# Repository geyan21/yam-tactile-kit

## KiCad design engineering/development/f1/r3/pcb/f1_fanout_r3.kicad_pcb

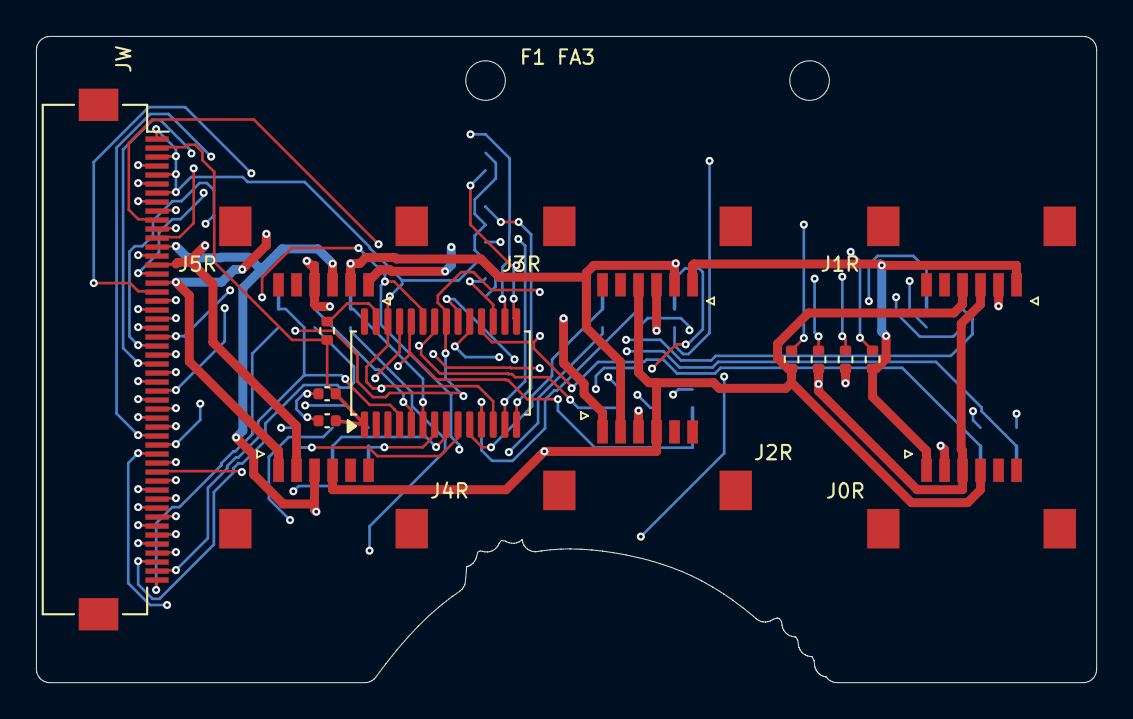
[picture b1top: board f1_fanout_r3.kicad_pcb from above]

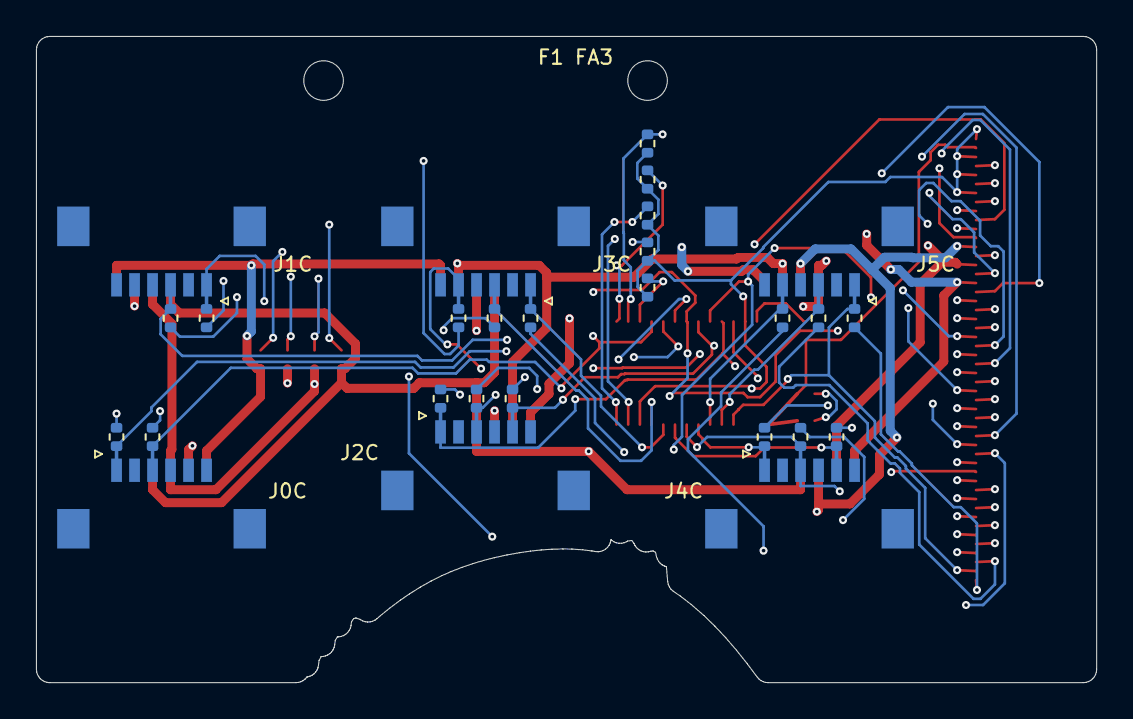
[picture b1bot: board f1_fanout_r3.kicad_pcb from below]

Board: 4 copper layers, 58.9 x 35.9 mm, 44 parts (27 on the bottom side), 48 nets.

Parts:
CT1: 100 nF X7R 10 V; CT1
CT2: 1 uF X7R 10 V; CT2
H1, H2: M2 clearance; MOUNT_M2
J0C: FH12-6S-1SH(1)(98); J0C
J0R: FH12-6S-1SH(1)(98); J0R
J1C: FH12-6S-1SH(1)(98); J1C
J1R: FH12-6S-1SH(1)(98); J1R
J2C: FH12-6S-1SH(1)(98); J2C
J2R: FH12-6S-1SH(1)(98); J2R
J3C: FH12-6S-1SH(1)(98); J3C
J3R: FH12-6S-1SH(1)(98); J3R
J4C: FH12-6S-1SH(1)(98); J4C
J4R: FH12-6S-1SH(1)(98); J4R
J5C: FH12-6S-1SH(1)(98); J5C
J5R: FH12-6S-1SH(1)(98); J5R
JW: FH12-50S-0.5SH(55); JW
RKC0: 0 ohm sense pickoff; RKC0
RKC1: 0 ohm sense pickoff; RKC1
RKC2: 0 ohm sense pickoff; RKC2
RKC3: 0 ohm sense pickoff; RKC3
RKC4: 0 ohm sense pickoff; RKC4
RKC5: 0 ohm sense pickoff; RKC5
RKC6: 0 ohm sense pickoff; RKC6
RKC7: 0 ohm sense pickoff; RKC7
RKC8: 0 ohm sense pickoff; RKC8
RKC9: 0 ohm sense pickoff; RKC9
RKC10: 0 ohm sense pickoff; RKC10
RKC11: 0 ohm sense pickoff; RKC11
RKC12: 0 ohm sense pickoff; RKC12
RKC13: 0 ohm sense pickoff; RKC13
RKC14: 0 ohm sense pickoff; RKC14
RKC15: 0 ohm sense pickoff; RKC15
RKR0: 0 ohm sense pickoff; RKR0
RKR1: 0 ohm sense pickoff; RKR1
RKR2: 0 ohm sense pickoff; RKR2
RKR3: 0 ohm sense pickoff; RKR3
RP0: 100k; RP0
RP1: 100k; RP1
RP2: 100k; RP2
RP3: 100k; RP3
RP4: 100k; RP4
RT: 10.0k 0.1% 25ppm/K; RT
UT: ADG706BRUZ; UT

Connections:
+3V3: CT1.1, CT2.1, JW.2, RT.1, UT.1
A0: JW.4, RP0.1, UT.16
A1: JW.6, RP1.1, UT.15
A2: JW.8, RP2.1, UT.14
A3: JW.9, RP3.1, UT.13
C0_I: J0C.3, JW.19, RKC0.1, UT.18
C0_S: JW.20, RKC0.2
C1_I: J0C.1, JW.21, RKC1.1, UT.19
C1_S: JW.22, RKC1.2
C2_I: J1C.3, JW.23, RKC2.1, UT.20
C2_S: JW.24, RKC2.2
C3_I: J1C.1, JW.25, RKC3.1, UT.21
C3_S: JW.26, RKC3.2
C4_I: J2C.5, JW.27, RKC4.1, UT.22
C4_S: JW.28, RKC4.2
C5_I: J2C.3, JW.29, RKC5.1, UT.23
C5_S: JW.30, RKC5.2
C6_I: J2C.1, JW.31, RKC6.1, UT.24
C6_S: JW.32, RKC6.2
C7_I: J3C.5, JW.33, RKC7.1, UT.25
C7_S: JW.34, RKC7.2
C8_I: J3C.3, JW.35, RKC8.1, UT.11
C8_S: JW.36, RKC8.2
C9_I: J3C.1, JW.37, RKC9.1, UT.10
C9_S: JW.38, RKC9.2
C10_I: J4C.5, JW.39, RKC10.1, UT.9
C10_S: JW.40, RKC10.2
C11_I: J4C.3, JW.41, RKC11.1, UT.8
C11_S: JW.42, RKC11.2
C12_I: J4C.1, JW.43, RKC12.1, UT.7
C12_S: JW.44, RKC12.2
C13_I: J5C.5, JW.45, RKC13.1, UT.6
C13_S: JW.46, RKC13.2
C14_I: J5C.3, JW.47, RKC14.1, UT.5
C14_S: JW.48, RKC14.2
C15_I: J5C.1, JW.49, RKC15.1, UT.4
C15_S: JW.50, RKC15.2
GND: CT1.2, CT2.2, JW.1, JW.3, JW.5, JW.7, RP0.2, RP1.2, RP2.2, RP3.2, RP4.2, UT.12, UT.26
R0_I: J0R.4, J1R.4, J2R.4, J3R.4, J4R.4, J5R.4, JW.11, RKR0.1
R0_S: JW.12, RKR0.2
R1_I: J0R.3, J1R.3, J2R.3, J3R.3, J4R.3, J5R.3, JW.13, RKR1.1
R1_S: JW.14, RKR1.2
R2_I: J0R.2, J1R.2, J2R.2, J3R.2, J4R.2, J5R.2, JW.15, RKR2.1
R2_S: JW.16, RKR2.2
R3_I: J0R.1, J1R.1, J2R.1, J3R.1, J4R.1, J5R.1, JW.17, RKR3.1
R3_S: JW.18, RKR3.2
TEST_D: RT.2, UT.27
TEST_EN: JW.10, RP4.1, UT.17

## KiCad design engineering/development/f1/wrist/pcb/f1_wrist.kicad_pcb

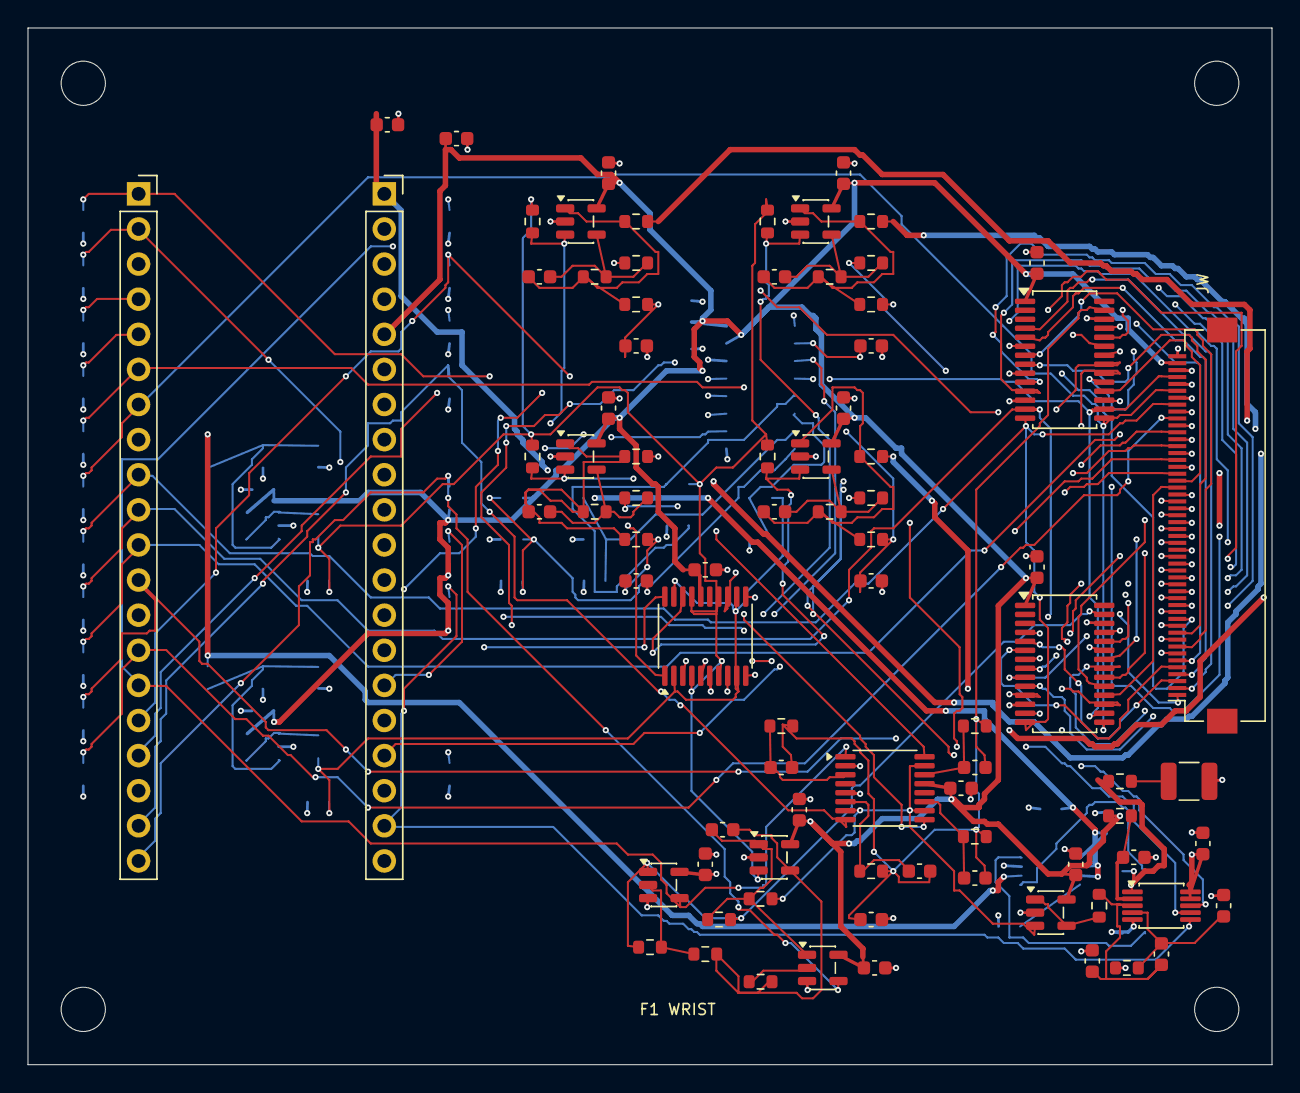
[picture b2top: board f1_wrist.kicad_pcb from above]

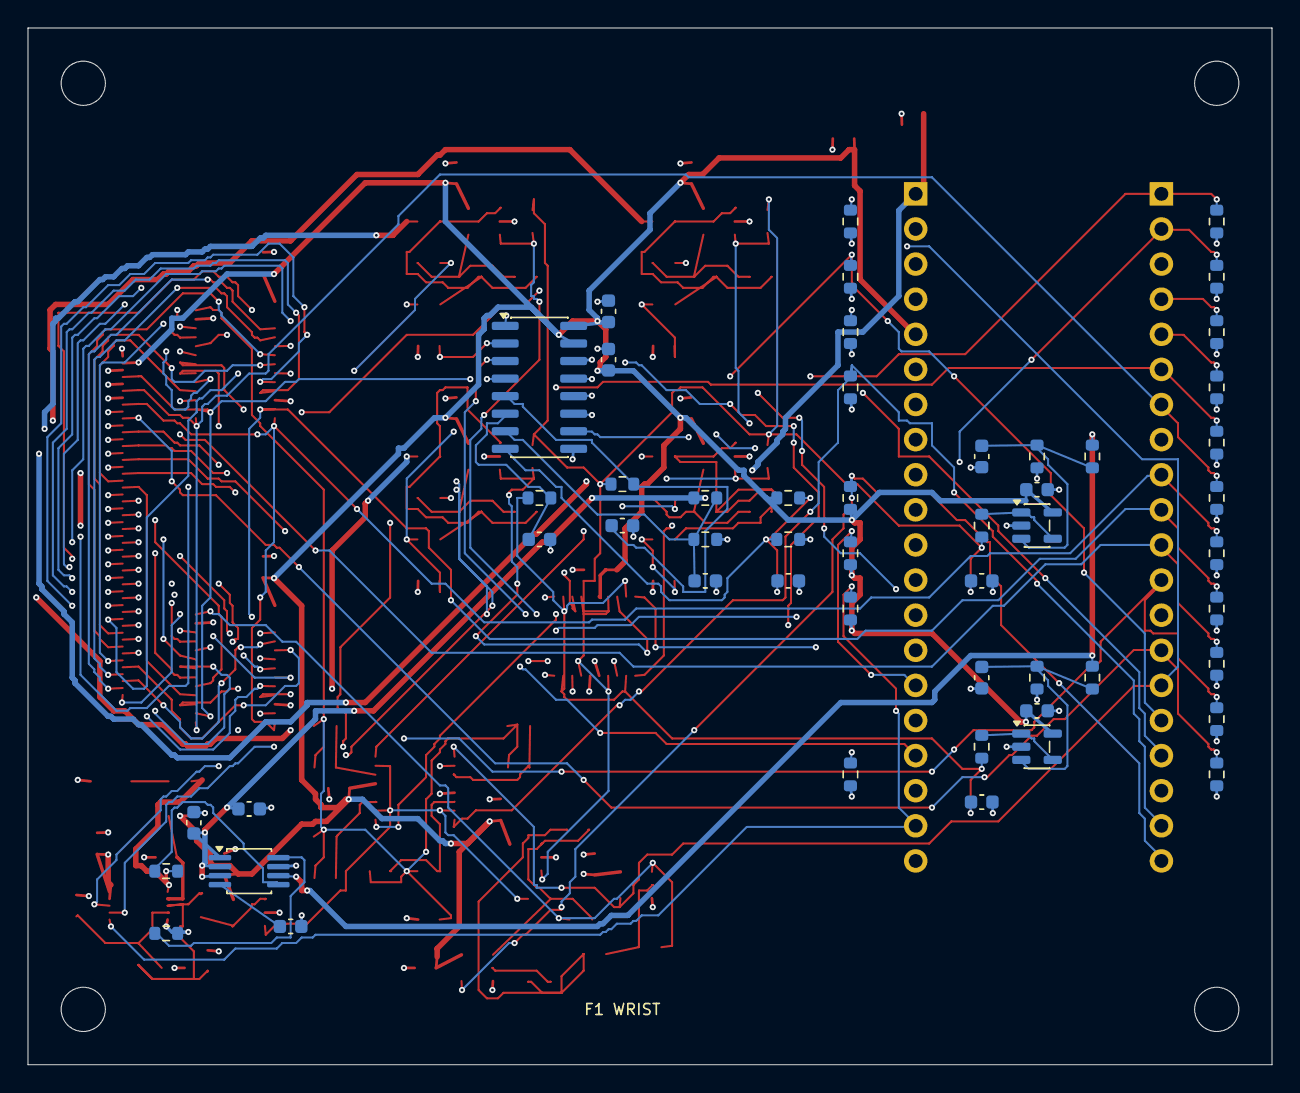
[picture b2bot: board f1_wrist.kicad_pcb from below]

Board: 4 copper layers, 90.0 x 75.0 mm, 139 parts (52 on the bottom side), 110 nets.

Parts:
CADCD: 2.2n C0G; CADCD
CADCN: 2.2n C0G; CADCN
CADCP: 2.2n C0G; CADCP
CAVDD: 1u X7R 10V; CAVDD
CBIASIN: 100n X7R 10V; CBIASIN
CBIASOUT: 100n X7R 10V; CBIASOUT
CBMON: 1u X7R 10V; CBMON
CBULK3: 10u X7R 10V; CBULK3
CBULK5: 4.7u X7R 10V; CBULK5
CCURRENT: 3.3n C0G; CCURRENT
CDAB: 100n X7R 10V; CDAB
CDBIAS: 100n X7R 10V; CDBIAS
CDBYP: 100n X7R 10V; CDBYP
CDEXC: 100n X7R 10V; CDEXC
CDGAIN: 100n X7R 10V; CDGAIN
CDMON: 100n X7R 10V; CDMON
CDPARK: 100n X7R 10V; CDPARK
CDR0: 100n X7R 10V; CDR0
CDR1: 100n X7R 10V; CDR1
CDR2: 100n X7R 10V; CDR2
CDR3: 100n X7R 10V; CDR3
CDTIA: 100n X7R 10V; CDTIA
CDVDD: 1u X7R 10V; CDVDD
CEXCIN: 100n X7R 10V; CEXCIN
CEXCOUT: 100n X7R 10V; CEXCOUT
CFB0: 100p C0G; CFB0
CFB1: 100p C0G; CFB1
CFB2: 100p C0G; CFB2
CFB3: 100p C0G; CFB3
CFILT: 2.2u X7R 10V; effective >=1u; CFILT
CLOCAL: 15p C0G; CLOCAL
CMB: 10n X7R 10V; CMB
CME: 10n X7R 10V; CME
CMON0: 10n X7R 10V; CMON0
CMON1: 10n X7R 10V; CMON1
CMON2: 10n X7R 10V; CMON2
CMON3: 10n X7R 10V; CMON3
CREF: 22u X7R 25V; effective 10-47u verified; CREF
CREFIN1: 100n X7R 10V; CREFIN1
CREFIN2: 1u X7R 10V; CREFIN2
CRSEL: 100n X7R 10V; CRSEL
CTIA0: 470p C0G; CTIA0
CTIA1: 150p C0G; CTIA1
CTIA2: 68p C0G; CTIA2
CTIA3: 56p C0G; CTIA3
CUCI: 100n X7R 10V; CUCI
CUCS: 100n X7R 10V; CUCS
CV3: 10n X7R 10V; CV3
CV5: 10n X7R 10V; CV5
H1, H2, H3, H4: (no value)
JP1: 1x20 female socket 2.54 mm; Pico header; JP1
JP2: 1x20 female socket 2.54 mm; Pico header; JP2
JW: FH12-50S-0.5SH(55); JW
PD_A0: 100k; PD_A0
PD_A1: 100k; PD_A1
PD_A2: 100k; PD_A2
PD_A3: 100k; PD_A3
PD_CUR_EN: 100k; PD_CUR_EN
PD_GAIN0: 100k; PD_GAIN0
PD_GAIN1: 100k; PD_GAIN1
PD_GAIN2: 100k; PD_GAIN2
PD_GAIN3: 100k; PD_GAIN3
PD_MISO: 100k; PD_MISO
PD_ROW0: 100k; PD_ROW0
PD_ROW1: 100k; PD_ROW1
PD_ROW2: 100k; PD_ROW2
PD_ROW3: 100k; PD_ROW3
PD_SNS_EN: 100k; PD_SNS_EN
PD_TEST_EN: 100k; PD_TEST_EN
PU_ADC_CONV: 100k; PU_ADC_CONV
PU_MON_CS: 100k; PU_MON_CS
PU_PARK: 100k; PU_PARK
RACTIVEPARK: 1k; RACTIVEPARK
RADCN: 22 0.1%; RADCN
RADCP: 22 0.1%; RADCP
RAVDD: 2.2; RAVDD
RBIAS0: 1M; RBIAS0
RBIAS1: 1M; RBIAS1
RBIAS2: 1M; RBIAS2
RBIAS3: 1M; RBIAS3
RBIASB: 10000 0.01% 10ppm/K; RBIASB
RBIASOUT: 47; RBIASOUT
RBIAST: 10000 0.01% 10ppm/K; RBIAST
RBOOST: 680; RBOOST
REXCB: 17000 0.01% 10ppm/K; REXCB
REXCOUT: 47; REXCOUT
REXCT: 16000 0.01% 10ppm/K; REXCT
RFB0: 100M; RFB0
RFB1: 100M; RFB1
RFB2: 100M; RFB2
RFB3: 100M; RFB3
RGNDS: 0 sense pickup; RGNDS
RINPUT: 300; RINPUT
RISO0: 47; RISO0
RISO1: 47; RISO1
RISO2: 47; RISO2
RISO3: 47; RISO3
RMB: 4.7k; RMB
RME: 4.7k; RME
RMON0: 4.7k; RMON0
RMON1: 4.7k; RMON1
RMON2: 4.7k; RMON2
RMON3: 4.7k; RMON3
ROUT: 0.1; ROUT
RPARK: 100M; RPARK
RREFESR: 0.047 1%; RREFESR
RREFS: 0 sense pickup; RREFS
RSNS0: 4700; RSNS0
RSNS1: 4700; RSNS1
RSNS2: 4700; RSNS2
RSNS3: 4700; RSNS3
RTIA0: 499 0.1%; RTIA0
RTIA1: 4990 0.1%; RTIA1
RTIA2: 24900 0.1%; RTIA2
RTIA3: 39200 0.1%; RTIA3
RV3B: 10k 0.1%; RV3B
RV3T: 10k 0.1%; RV3T
RV5B: 10k 0.1%; RV5B
RV5T: 10k 0.1%; RV5T
UAB: OPA320AQDBVRQ1; UAB
UADC: ADS8866IDGSR; UADC
UBIAS: OPA392DBVR; UBIAS
UBYP: TMUX1102DBVR; UBYP
UCI: ADG706BRUZ; UCI
UCS: ADG706BRUZ; UCS
UEXC: OPA392DBVR; UEXC
UGAIN: TMUX1112PWR; UGAIN
UMON: MCP3208-B/SL; UMON
UPARK: TMUX1101DBVR; UPARK
UR0: OPA392DBVR; UR0
UR1: OPA392DBVR; UR1
UR2: OPA392DBVR; UR2
UR3: OPA392DBVR; UR3
UREF: REF6033IDGKR; UREF
URSEL: TMUX1134PWR; URSEL
UTIA: OPA392DBVR; UTIA

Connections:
+3V3: CBMON.1, CBULK3.1, CDAB.1, CDBIAS.1, CDBYP.1, CDEXC.1, CDGAIN.1, CDMON.1, CDPARK.1, CDR0.1, CDR1.1, CDR2.1, CDR3.1, CDTIA.1, CDVDD.1, CRSEL.1, CUCI.1, CUCS.1, JP2.5, JW.49, PU_ADC_CONV.2, PU_MON_CS.2, PU_PARK.2, RAVDD.1, RV3T.1, UAB.5, UADC.9, UADC.10, UBIAS.5, UBYP.5, UCI.1, UCS.1, UEXC.5, UGAIN.13, UMON.15, UMON.16, UPARK.5, UR0.5, UR1.5, UR2.5, UR3.5, URSEL.16, UTIA.5
+3V3_DIV2: CV3.1, RV3B.1, RV3T.2, UMON.8
+5V: CBULK5.1, CREFIN1.1, CREFIN2.1, JP2.1, RV5T.1, UREF.1, UREF.2, UREF.3
+5V_DIV2: CV5.1, RV5B.1, RV5T.2, UMON.7
A0: JP1.6, JW.47, PD_A0.1, UCI.16, UCS.16
A1: JP1.7, JW.45, PD_A1.1, UCI.15, UCS.15
A2: JP1.9, JW.43, PD_A2.1, UCI.14, UCS.14
A3: JP1.10, JW.42, PD_A3.1, UCI.13, UCS.13
ADC_AVDD: CAVDD.1, RAVDD.2, UADC.2
ADC_BUFFER: RADCP.1, UAB.1, UAB.4
ADC_CONV: JP2.19, PU_ADC_CONV.1, UADC.6
AINN: CADCD.2, CADCN.1, RADCN.2, UADC.4
AINP: CADCD.1, CADCP.1, RADCP.2, UADC.3
AMP_OUT: CLOCAL.1, ROUT.1, RPARK.1, UPARK.1, UTIA.1
BIAS_BUFFER: RBIASOUT.1, UBIAS.1, UBIAS.4
BIAS_DIV: CBIASIN.1, RBIASB.1, RBIAST.2, UBIAS.3
BIAS_MON: CMB.1, RMB.2, UMON.5
C0_I: JW.32, UCI.18
C0_S: JW.31, UCS.18
C1_I: JW.30, UCI.19
C1_S: JW.29, UCS.19
C2_I: JW.28, UCI.20
C2_S: JW.27, UCS.20
C3_I: JW.26, UCI.21
C3_S: JW.25, UCS.21
C4_I: JW.24, UCI.22
C4_S: JW.23, UCS.22
C5_I: JW.22, UCI.23
C5_S: JW.21, UCS.23
C6_I: JW.20, UCI.24
C6_S: JW.19, UCS.24
C7_I: JW.18, UCI.25
C7_S: JW.17, UCS.25
C8_I: JW.16, UCI.11
C8_S: JW.15, UCS.11
C9_I: JW.14, UCI.10
C9_S: JW.13, UCS.10
C10_I: JW.12, UCI.9
C10_S: JW.11, UCS.9
C11_I: JW.10, UCI.8
C11_S: JW.9, UCS.8
C12_I: JW.8, UCI.7
C12_S: JW.7, UCS.7
C13_I: JW.6, UCI.6
C13_S: JW.5, UCS.6
C14_I: JW.4, UCI.5
C14_S: JW.3, UCS.5
C15_I: JW.2, UCI.4
C15_S: JW.1, UCS.4
COMP_MID: RBOOST.2, RINPUT.1, UBYP.2
CURRENT_D: CCURRENT.1, CTIA0.2, CTIA1.2, CTIA2.2, CTIA3.2, RTIA0.2, RTIA1.2, RTIA2.2, RTIA3.2, UCI.27
CUR_EN: JP1.11, PD_CUR_EN.1, UCI.17
EXCITE_MON: CME.1, RME.2, UMON.6
EXC_BUFFER: REXCOUT.1, UEXC.1, UEXC.4
EXC_DIV: CEXCIN.1, REXCB.1, REXCT.2, UEXC.3
GAIN0: JP1.15, PD_GAIN0.1, UBYP.4, UGAIN.1
GAIN1: JP1.16, PD_GAIN1.1, UGAIN.16
GAIN2: JP1.17, PD_GAIN2.1, UGAIN.9
GAIN3: JP1.19, PD_GAIN3.1, UGAIN.8
GAIN_BRANCH0: CTIA0.1, RTIA0.1, UGAIN.3
GAIN_BRANCH1: CTIA1.1, RTIA1.1, UGAIN.14
GAIN_BRANCH2: CTIA2.1, RTIA2.1, UGAIN.11
GAIN_BRANCH3: CTIA3.1, RTIA3.1, UGAIN.6
GND: CADCN.2, CADCP.2, CAVDD.2, CBIASIN.2, CBIASOUT.2, CBMON.2, CBULK3.2, CBULK5.2, CCURRENT.2, CDAB.2, CDBIAS.2, CDBYP.2, CDEXC.2, CDGAIN.2, CDMON.2, CDPARK.2, CDR0.2, CDR1.2, CDR2.2, CDR3.2, CDTIA.2, CDVDD.2, CEXCIN.2, CEXCOUT.2, CFILT.2, CMB.2, CME.2, CMON0.2, CMON1.2, CMON2.2, CMON3.2, CREF.2, CREFIN1.2, CREFIN2.2, CRSEL.2, CUCI.2, CUCS.2, CV3.2, CV5.2, JP1.3, JP1.8, JP1.13, JP1.18, JP2.3, JP2.8, JP2.13, JP2.18, JW.44, JW.46, JW.48, JW.50, PD_A0.2, PD_A1.2, PD_A2.2, PD_A3.2, PD_CUR_EN.2, PD_GAIN0.2, PD_GAIN1.2, PD_GAIN2.2, PD_GAIN3.2, PD_MISO.2, PD_ROW0.2, PD_ROW1.2, PD_ROW2.2, PD_ROW3.2, PD_SNS_EN.2, PD_TEST_EN.2, RADCN.1, RBIASB.2, REXCB.2, RGNDS.2, RV3B.2, RV5B.2, UAB.2, UADC.5, UBIAS.2, UBYP.3, UCI.12, UCI.26, UCS.12, UCS.26, UEXC.2, UGAIN.5, UMON.9, UMON.14, UPARK.3, UR0.2, UR1.2, UR2.2, UR3.2, UREF.7, URSEL.5, URSEL.6, UTIA.2
MON_CS: JP2.15, PU_MON_CS.1, UMON.10
OUTPUT_BUS: ROUT.2, UAB.3, UGAIN.2, UGAIN.7, UGAIN.10, UGAIN.15
PARK: JP1.20, PU_PARK.1, UPARK.4
PARK_LINK: RACTIVEPARK.1, UPARK.2
R0_I: JW.40, RISO0.2
R0_S: JW.39, RSNS0.1
R1_I: JW.38, RISO1.2
R1_S: JW.37, RSNS1.1
R2_I: JW.36, RISO2.2
R2_S: JW.35, RSNS2.1
R3_I: JW.34, RISO3.2
R3_S: JW.33, RSNS3.1
REF_CAP: CREF.1, RREFESR.2
REF_FILT: CFILT.1, UREF.4
REF_GND_SENSE: RGNDS.1, UREF.8
ROW0: JP1.1, PD_ROW0.1, URSEL.1
ROW0_CMD: RBIAS0.1, UR0.3, URSEL.3
ROW0_FB: CFB0.2, RFB0.2, RSNS0.2, UR0.4
ROW0_MON: CMON0.1, RMON0.2, UMON.1
ROW0_OUT: CFB0.1, RFB0.1, RISO0.1, RMON0.1, UR0.1
ROW1: JP1.2, PD_ROW1.1, URSEL.10
ROW1_CMD: RBIAS1.1, UR1.3, URSEL.8
ROW1_FB: CFB1.2, RFB1.2, RSNS1.2, UR1.4
ROW1_MON: CMON1.1, RMON1.2, UMON.2
ROW1_OUT: CFB1.1, RFB1.1, RISO1.1, RMON1.1, UR1.1
ROW2: JP1.4, PD_ROW2.1, URSEL.11
ROW2_CMD: RBIAS2.1, UR2.3, URSEL.13
ROW2_FB: CFB2.2, RFB2.2, RSNS2.2, UR2.4
ROW2_MON: CMON2.1, RMON2.2, UMON.3
ROW2_OUT: CFB2.1, RFB2.1, RISO2.1, RMON2.1, UR2.1
ROW3: JP1.5, PD_ROW3.1, URSEL.20
ROW3_CMD: RBIAS3.1, UR3.3, URSEL.18
ROW3_FB: CFB3.2, RFB3.2, RSNS3.2, UR3.4
ROW3_MON: CMON3.1, RMON3.2, UMON.4
ROW3_OUT: CFB3.1, RFB3.1, RISO3.1, RMON3.1, UR3.1
SENSE_D: RBOOST.1, RPARK.2, UBYP.1, UCS.27
SNS_EN: JP1.12, PD_SNS_EN.1, UCS.17
SPI_MISO: JP2.20, PD_MISO.1, UADC.7, UMON.12
SPI_MOSI: JP2.16, UMON.11
SPI_SCK: JP2.17, UADC.8, UMON.13
TEST_EN: JP1.14, JW.41, PD_TEST_EN.1
TIA_FB: CLOCAL.2, RACTIVEPARK.2, RINPUT.2, UTIA.4
VBIAS: CBIASOUT.1, RBIAS0.2, RBIAS1.2, RBIAS2.2, RBIAS3.2, RBIASOUT.2, RMB.1, URSEL.4, URSEL.7, URSEL.14, URSEL.17, UTIA.3
VEXCITE: CEXCOUT.1, REXCOUT.2, RME.1, URSEL.2, URSEL.9, URSEL.12, URSEL.19
VREF33: RBIAST.1, REXCT.1, RREFESR.1, RREFS.2, UADC.1, UREF.6
VREF_SENSE: RREFS.1, UREF.5

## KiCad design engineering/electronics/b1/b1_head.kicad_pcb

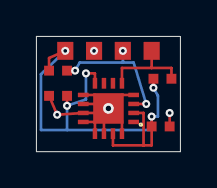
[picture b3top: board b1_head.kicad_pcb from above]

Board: 2 copper layers, 8.0 x 6.4 mm, 6 parts (0 on the bottom side), 4 nets.

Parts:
C1: 100nF 16V X7R 0402; C1
C2: 100nF 16V X7R 0402; C2
J1: Solder wires 3V3 GND SCL SDA; J1
R1: 10k 1% 0402; R1
R2: 10k 1% 0402; R2
U1: MLX90393SLW-ABA-011; U1

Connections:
3V3: C1.1, C2.2, J1.1, R1.1, R2.1, U1.2, U1.8, U1.15
GND: C1.2, C2.1, J1.2, U1.4, U1.9, U1.10, U1.11, U1.12, U1.13, U1.14, U1.16, U1.17
SCL: J1.3, R1.2, U1.3
SDA: J1.4, R2.2, U1.5

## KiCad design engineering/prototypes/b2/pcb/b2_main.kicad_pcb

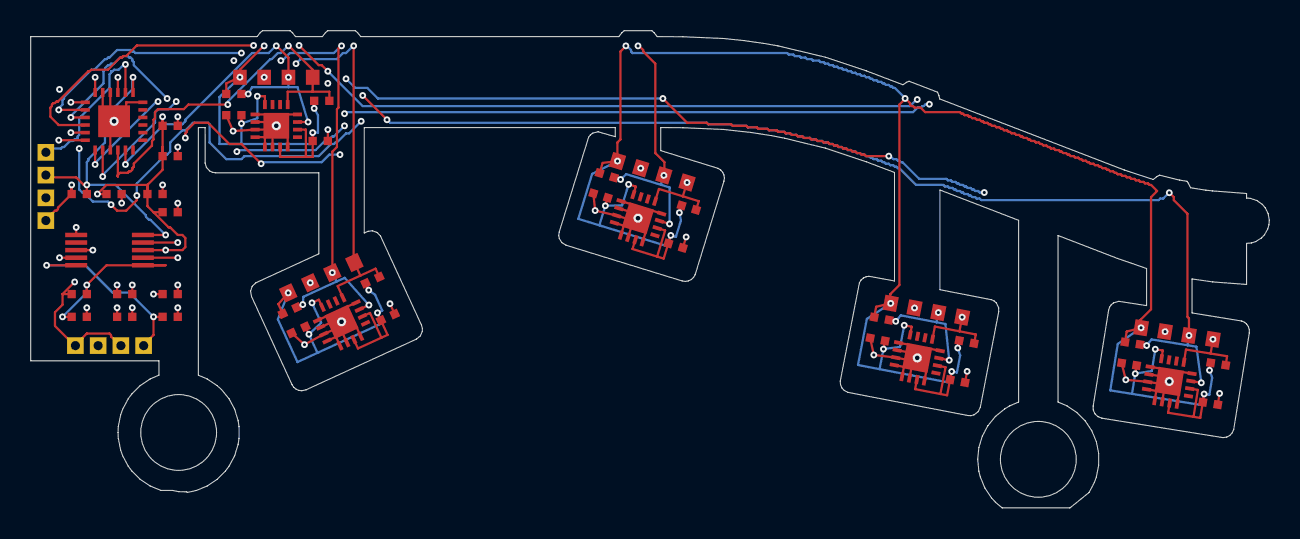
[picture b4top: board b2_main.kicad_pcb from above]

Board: 4 copper layers, 81.7 x 31.5 mm, 46 parts (0 on the bottom side), 19 nets.

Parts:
C11: 100nF 16V X7R 0402; C11
C12: 100nF 16V X7R 0402; C12
C21: 100nF 16V X7R 0402; C21
C22: 100nF 16V X7R 0402; C22
C31: 100nF 16V X7R 0402; C31
C32: 100nF 16V X7R 0402; C32
C41: 100nF 16V X7R 0402; C41
C42: 100nF 16V X7R 0402; C42
C51: 100nF 16V X7R 0402; C51
C52: 100nF 16V X7R 0402; C52
C100: 100nF 16V X7R 0402; C100
C101: 100nF 16V X7R 0402; C101
C102: 1uF 10V X7R 0402; C102
J1: Rear-exit solder wires; J1
J2: Rear-exit solder wires; J2
R11: 10k 1% 0402; R11
R12: 10k 1% 0402; R12
R21: 10k 1% 0402; R21
R22: 10k 1% 0402; R22
R31: 10k 1% 0402; R31
R32: 10k 1% 0402; R32
R41: 10k 1% 0402; R41
R42: 10k 1% 0402; R42
R51: 10k 1% 0402; R51
R52: 10k 1% 0402; R52
R100: 4.7k 1% 0402; R100
R101: 4.7k 1% 0402; R101
R102: 10k 1% 0402; R102
R103: 10k 1% 0402; R103
R104: 10k 1% 0402; R104
R105: 10k 1% 0402; R105
R106: 10k 1% 0402; R106
R107: 10k 1% 0402; R107
R108: 10k 1% 0402; R108
TP1: Solder wires 3V3 GND SCL SDA; TP1
TP2: Solder wires 3V3 GND SCL SDA; TP2
TP3: Solder wires 3V3 GND SCL SDA; TP3
TP4: Solder wires 3V3 GND SCL SDA; TP4
TP5: Solder wires 3V3 GND SCL SDA; TP5
U1: MLX90393SLW-ABA-011; U1
U2: MLX90393SLW-ABA-011; U2
U3: MLX90393SLW-ABA-011; U3
U4: MLX90393SLW-ABA-011; U4
U5: MLX90393SLW-ABA-011; U5
U10: TCA9548ARGER; U10
U11: ADS1115IDGSR; U11

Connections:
3V3: C11.1, C12.2, C21.1, C22.2, C31.1, C32.2, C41.1, C42.2, C51.1, C52.2, C100.1, C101.1, C102.1, J1.1, J2.1, J2.3, R11.1, R12.1, R21.1, R22.1, R31.1, R32.1, R41.1, R42.1, R51.1, R52.1, R100.1, R101.1, R102.1, R103.1, R105.1, TP1.1, TP2.1, TP3.1, TP4.1, TP5.1, U1.2, U1.8, U1.15, U2.2, U2.8, U2.15, U3.2, U3.8, U3.15, U4.2, U4.8, U4.15, U5.2, U5.8, U5.15, U10.21, U11.8
CHECK_HALF: R105.2, R106.1, U11.7
GND: C11.2, C12.1, C21.2, C22.1, C31.2, C32.1, C41.2, C42.1, C51.2, C52.1, C100.2, C101.2, C102.2, J1.2, R104.2, R106.2, R107.2, R108.2, TP1.2, TP2.2, TP3.2, TP4.2, TP5.2, U1.4, U1.9, U1.10, U1.11, U1.12, U1.13, U1.14, U1.16, U1.17, U2.4, U2.9, U2.10, U2.11, U2.12, U2.13, U2.14, U2.16, U2.17, U3.4, U3.9, U3.10, U3.11, U3.12, U3.13, U3.14, U3.16, U3.17, U4.4, U4.9, U4.10, U4.11, U4.12, U4.13, U4.14, U4.16, U4.17, U5.4, U5.9, U5.10, U5.11, U5.12, U5.13, U5.14, U5.16, U5.17, U10.9, U10.18, U10.22, U10.23, U10.25, U11.1, U11.3
RESET: R102.2, U10.24
SCL: J1.3, R100.2, U10.19, U11.10
SCL0: R11.2, TP1.3, U1.3, U10.2
SCL1: R21.2, TP2.3, U2.3, U10.4
SCL2: R31.2, TP3.3, U3.3, U10.6
SCL3: R41.2, TP4.3, U4.3, U10.8
SCL4: R51.2, TP5.3, U5.3, U10.11
SDA: J1.4, R101.2, U10.20, U11.9
SDA0: R12.2, TP1.4, U1.5, U10.1
SDA1: R22.2, TP2.4, U2.5, U10.3
SDA2: R32.2, TP3.4, U3.5, U10.5
SDA3: R42.2, TP4.4, U4.5, U10.7
SDA4: R52.2, TP5.4, U5.5, U10.10
T0: J2.2, R107.1, U11.4
T1: J2.4, R108.1, U11.5
VDD_HALF: R103.2, R104.1, U11.6

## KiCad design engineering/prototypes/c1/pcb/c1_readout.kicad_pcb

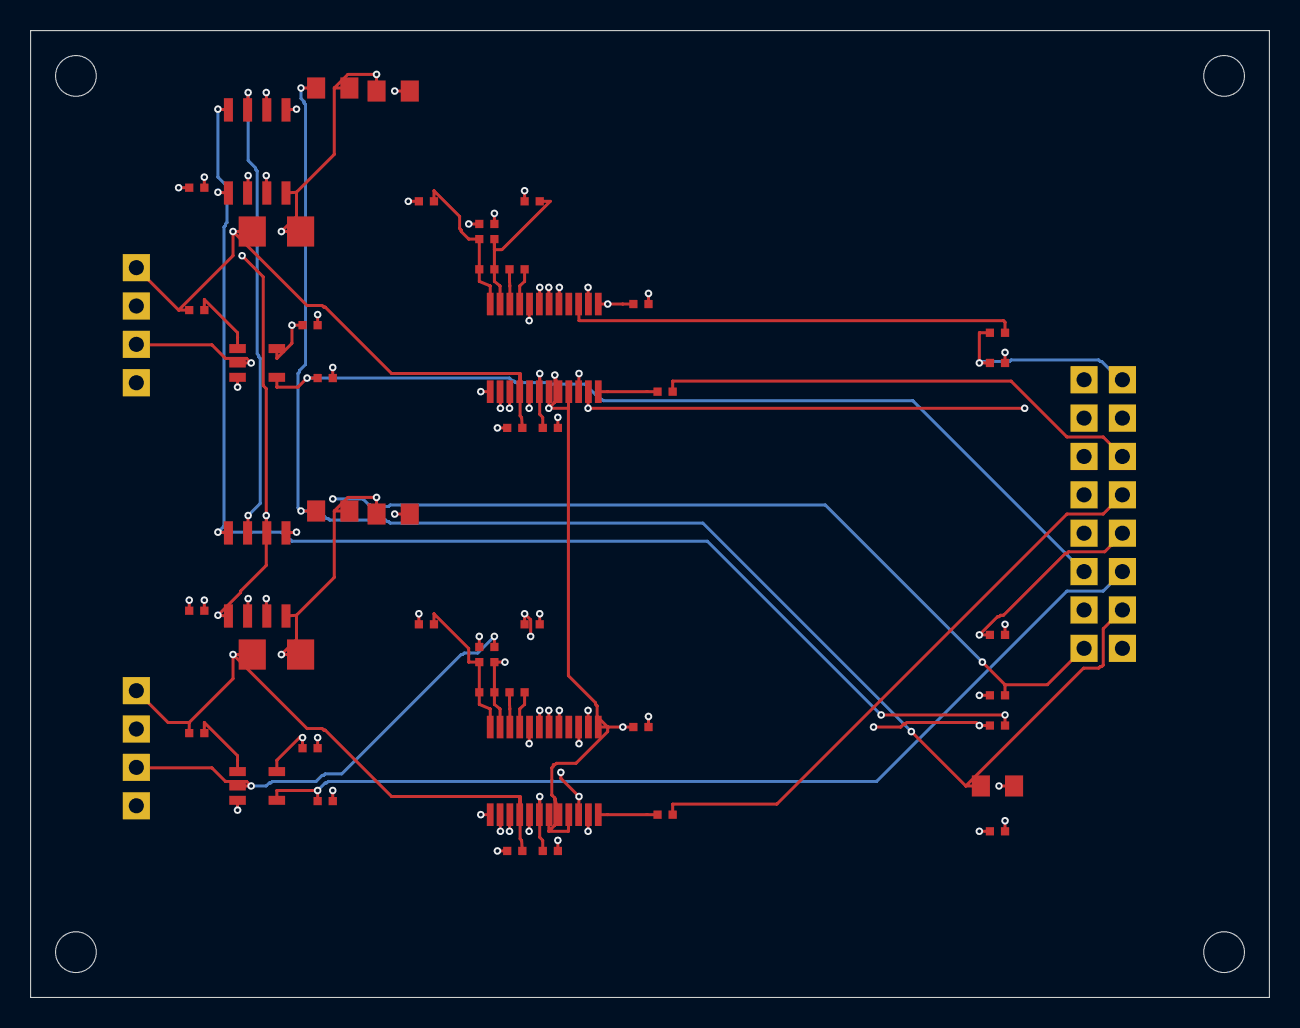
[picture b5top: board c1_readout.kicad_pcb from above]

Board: 4 copper layers, 82.0 x 64.0 mm, 50 parts (0 on the bottom side), 34 nets.

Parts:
C3: 1uF 10V X7R 0402; C3
C5: 10uF 10V X7R 0805; C5
CAAV: 100nF X7R 0402; CAAV
CADIF: 10nF C0G 0402; CADIF
CADV: 100nF X7R 0402; CADV
CAMON: 100nF 16V X7R 0402; CAMON
CAPGA: 100nF X7R 0402; CAPGA
CAREF: 100nF X7R 0402; CAREF
CASUP: 10uF 10V X7R 0805; CASUP
CASW: 100nF 16V X7R 0402; CASW
CBAV: 100nF X7R 0402; CBAV
CBDIF: 10nF C0G 0402; CBDIF
CBDV: 100nF X7R 0402; CBDV
CBMON: 100nF 16V X7R 0402; CBMON
CBPGA: 100nF X7R 0402; CBPGA
CBREF: 100nF X7R 0402; CBREF
CBSUP: 10uF 10V X7R 0805; CBSUP
CBSW: 100nF 16V X7R 0402; CBSW
J1: 2.54mm through-hole header; J1
JA: 2.54mm through-hole header; JA
JB: 2.54mm through-hole header; JB
RABN: 10M 1% 0402; RABN
RABP: 10M 1% 0402; RABP
RACAL: 1M 0.1% 0402; RACAL
RAN: 100ohm 1% 0402; RAN
RAOUT: 33ohm 0402; RAOUT
RAP: 100ohm 1% 0402; RAP
RASEL: 100k 1% 0402; RASEL
RASH: 0.1ohm 1% 1206; RASH
RASUP: 10ohm 0805; RASUP
RBBN: 10M 1% 0402; RBBN
RBBP: 10M 1% 0402; RBBP
RBCAL: 1M 0.1% 0402; RBCAL
RBN: 100ohm 1% 0402; RBN
RBOUT: 33ohm 0402; RBOUT
RBP: 100ohm 1% 0402; RBP
RBSEL: 100k 1% 0402; RBSEL
RBSH: 0.1ohm 1% 1206; RBSH
RBSUP: 10ohm 0805; RBSUP
RCLK_A: 33ohm 0402; RCLK_A
RCLK_B: 33ohm 0402; RCLK_B
RPDWN: 100k 0402; RPDWN
RSCL: 4.7k 0402; RSCL
RSDA: 4.7k 0402; RSDA
UA: ADS1232IPWR; UA
UAMON: INA219AIDR; UAMON
UASW: TMUX1101DBVR; UASW
UB: ADS1232IPWR; UB
UBMON: INA219AIDR; UBMON
UBSW: TMUX1101DBVR; UBSW

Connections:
3V3: C3.1, CADV.1, CAMON.1, CBDV.1, CBMON.1, J1.13, RSCL.1, RSDA.1, UA.1, UA.19, UA.20, UA.21, UAMON.5, UB.1, UB.19, UB.20, UB.21, UBMON.2, UBMON.5
5V: C5.1, J1.14, RASUP.1, RBSUP.1
ADC_CLK: J1.2, RCLK_A.1, RCLK_B.1
A_AN: CADIF.1, RABN.2, RAN.2, UA.12
A_AP: CADIF.2, RABP.2, RAP.2, UA.11
A_CAP9: CAPGA.2, UA.9
A_CAP10: CAPGA.1, UA.10
A_CLK: RCLK_A.2, UA.3
A_DOUT: J1.6, RAOUT.2
A_DOUT_RAW: RAOUT.1, UA.24
A_E: CAREF.2, JA.1, RACAL.1, RASH.1, UA.16, UAMON.7
A_SHUNT: J1.11, RASEL.1, UASW.4
A_SHUNTED: RACAL.2, UASW.1
A_SN: JA.4, RAN.1
A_SP: JA.3, RAP.1, UASW.2
A_VA: CAAV.1, CASUP.1, CASW.1, RABP.1, RASH.2, RASUP.2, UA.18, UAMON.8, UASW.5
B_AN: CBDIF.1, RBBN.2, RBN.2, UB.12
B_AP: CBDIF.2, RBBP.2, RBP.2, UB.11
B_CAP9: CBPGA.2, UB.9
B_CAP10: CBPGA.1, UB.10
B_CLK: RCLK_B.2, UB.3
B_DOUT: J1.8, RBOUT.2
B_DOUT_RAW: RBOUT.1, UB.24
B_E: CBREF.2, JB.1, RBCAL.1, RBSH.1, UB.16, UBMON.7
B_SHUNT: J1.12, RBSEL.1, UBSW.4
B_SHUNTED: RBCAL.2, UBSW.1
B_SN: JB.4, RBN.1
B_SP: JB.3, RBP.1, UBSW.2
B_VA: CBAV.1, CBSUP.1, CBSW.1, RBBP.1, RBSH.2, RBSUP.2, UB.18, UBMON.8, UBSW.5
GND: C3.2, C5.2, CAAV.2, CADV.2, CAMON.2, CAREF.1, CASUP.2, CASW.2, CBAV.2, CBDV.2, CBMON.2, CBREF.1, CBSUP.2, CBSW.2, J1.1, J1.3, J1.5, J1.7, J1.9, JA.2, JB.2, RABN.1, RASEL.2, RBBN.1, RBSEL.2, RPDWN.2, UA.2, UA.5, UA.6, UA.7, UA.8, UA.13, UA.14, UA.15, UA.17, UAMON.1, UAMON.2, UAMON.6, UASW.3, UB.2, UB.5, UB.6, UB.7, UB.8, UB.13, UB.14, UB.15, UB.17, UBMON.1, UBMON.6, UBSW.3
PDWN: J1.10, RPDWN.1, UA.22, UB.22
SCL: J1.16, RSCL.2, UAMON.4, UBMON.4
SDA: J1.15, RSDA.2, UAMON.3, UBMON.3
SER_CLK: J1.4, UA.23, UB.23
